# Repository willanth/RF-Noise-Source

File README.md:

# RF-Noise-Source
Wideband noise source for calibrating RF equipment

Designed originally by Paul Meacham VK5AB

This circuit is designed to run from a 9V battery.  It is suggested that it be mounted inside a metal box for shielding purposes.
If the circuit is run from an external supply, it's suggested that the reverse polarity protection diode D1 be fitted.
For operation from a 9V battery, D1 may be omitted and jumped with a 0R resistor.

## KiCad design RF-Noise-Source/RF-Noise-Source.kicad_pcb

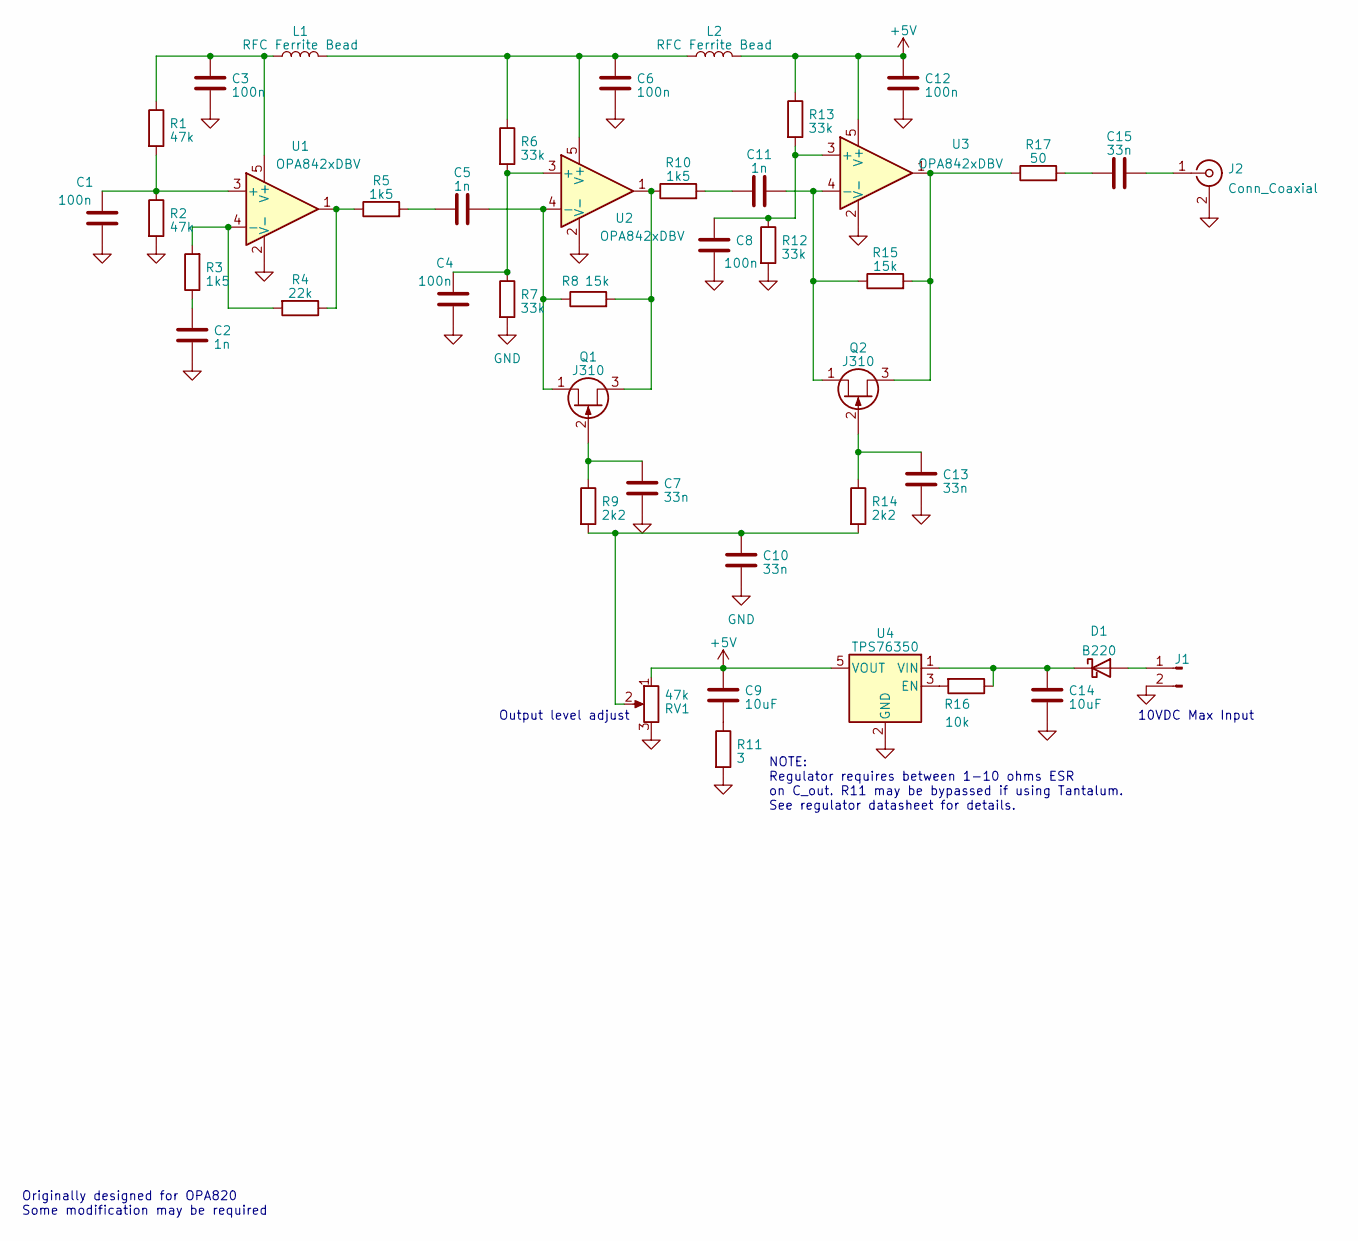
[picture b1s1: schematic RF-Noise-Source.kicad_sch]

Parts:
C1, C3, C4, C6, C8, C12: 100n; C_0603_1608Metric
C2, C5, C11: 1n; C_0603_1608Metric
C7, C10, C13, C15: 33n; C_0603_1608Metric
C9, C14: 10uF; C_0603_1608Metric
D1: B220; D_SMB
J1: Conn_01x02_Male; Molex_KK-254_AE-6410-02A_1x02_P2.54mm_Vertical
J2: Conn_Coaxial; SMA_Molex_73251-1153_EdgeMount_Horizontal
L1, L2: RFC Ferrite Bead; L_0805_2012Metric
Q1, Q2: J310; SOT-23
R1, R2: 47k; R_0603_1608Metric
R3, R5, R10: 1k5; R_0603_1608Metric
R4: 22k; R_0603_1608Metric
R6, R7, R12, R13: 33k; R_0603_1608Metric
R8, R15: 15k; R_0603_1608Metric
R9, R14: 2k2; R_0603_1608Metric
R11: 3; R_0603_1608Metric
R16: 10k; R_0603_1608Metric
R17: 50; R_0603_1608Metric
RV1: 47k; Potentiometer_Bourns_3214W_Vertical
U1, U2, U3: OPA842xDBV; SOT-23-5
U4: TPS76350; SOT-23-5

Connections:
+5V: C9.1, C12.1, L2.2, R13.1, RV1.1, U3.5 (V+), U4.5 (VOUT)
GND: C1.2, C2.2, C3.2, C4.2, C6.2, C7.2, C8.2, C10.2, C12.2, C13.2, C14.2, J1.2, J2.2 (Ext), R2.2, R7.2, R11.2, R12.2, RV1.3, U1.2 (V-), U2.2 (V-), U3.2 (V-), U4.2 (GND)
unnamed: C2.1, R3.1
unnamed: C5.1, R5.2
unnamed: C9.2, R11.1
unnamed: C10.1, R9.2, R14.2, RV1.2
unnamed: C11.1, R10.2
unnamed: C15.1, R17.2
unnamed: D1.2 (A), J1.1
unnamed: C14.1, D1.1 (K), R16.1, U4.1 (VIN)
unnamed: C15.2, J2.1 (In)
unnamed: C5.2, Q1.1 (D), R8.1, U2.4 (-)
unnamed: C7.1, Q1.2 (G), R9.1
unnamed: Q1.3 (S), R8.2, R10.1, U2.1
unnamed: C11.2, Q2.1 (D), R15.1, U3.4 (-)
unnamed: C13.1, Q2.2 (G), R14.1
unnamed: Q2.3 (S), R15.2, R17.1, U3.1
unnamed: R4.1, R5.1, U1.1
unnamed: C1.1, R1.2, R2.1, U1.3 (+)
unnamed: R3.2, R4.2, U1.4 (-)
unnamed: C3.1, L1.1, R1.1, U1.5 (V+)
unnamed: C4.1, R6.2, R7.1, U2.3 (+)
unnamed: C6.1, L1.2, L2.1, R6.1, U2.5 (V+)
unnamed: C8.1, R12.1, R13.2, U3.3 (+)
unnamed: R16.2, U4.3 (EN)

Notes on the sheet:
Output level adjust
10VDC Max Input
Originally designed for OPA820 Some modification may be required
NOTE: Regulator requires between 1-10 ohms ESR on C_out. R11 may be bypassed if using Tantalum. See regulator datasheet for details.

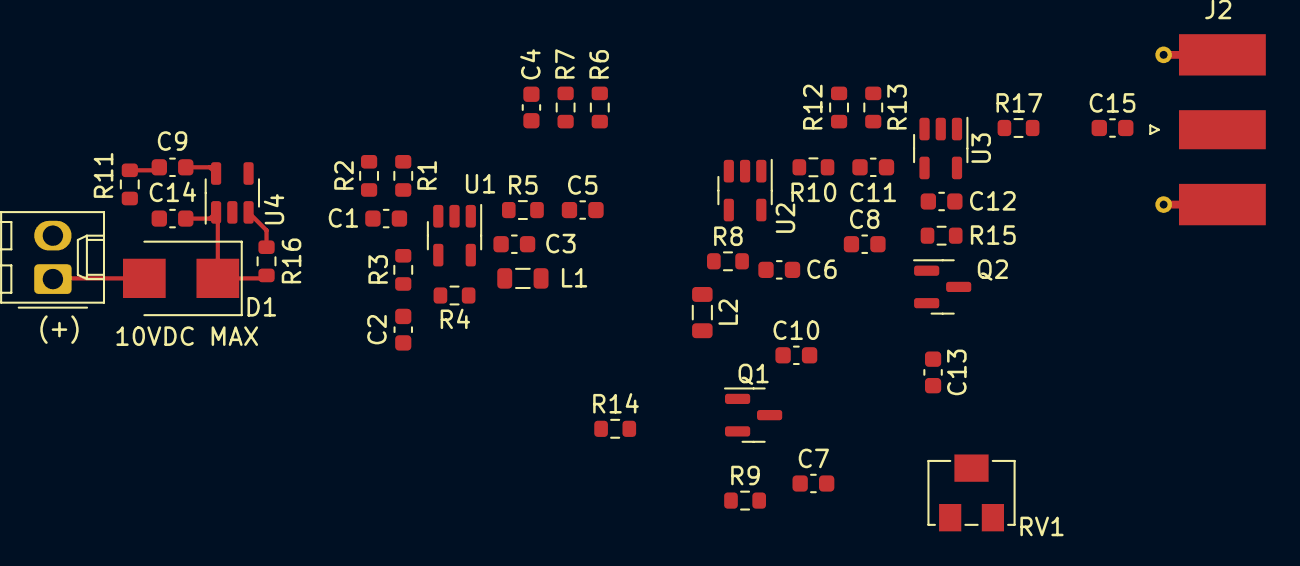
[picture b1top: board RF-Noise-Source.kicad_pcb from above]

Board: 2 copper layers, 44 parts (0 on the bottom side), 25 nets.

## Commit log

2022-01-09 schematic partially complete, component annotation/values/footprints are still required before moving to PCB design
2022-01-09 modified KiCad URL to be current
2023-04-14 schematic capture completed, beginning PCB layout
2023-04-14 had to merge from remote because I forgot to pull first. Added backup file folder to gitignore.
2023-04-14 preliminary PCB layout begun, basic blocking complete with some issues regarding signal routing.
